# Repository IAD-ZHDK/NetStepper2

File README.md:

# NetStepper2
A networked stepper motor controller based on the ESP-WROOM-32 and the L6470. Examples built with netStepper can be seen in this [video](https://vimeo.com/278343342).  

## Parts

### Controllers

- Stepper Controller: `L6470` ([Datasheet](https://www.mouser.com/ds/2/389/l6470-954753.pdf), [Mouser](https://www.mouser.ch/ProductDetail/STMicroelectronics/L6470H?qs=sGAEpiMZZMuP%2fQeRSdvksPGSQkvtk%2fGb))
- SoC: `ESP-WROOM-32` ([Datasheet](https://espressif.com/sites/default/files/documentation/esp-wroom-32_datasheet_en.pdf), [Mouser](https://www.mouser.ch/ProductDetail/Adafruit/3320?qs=%2fha2pyFaduhvAZY8Ie1SD0odCwfSxZwX5aiqddL%252ba6k%3d))
- USB/UART: `CP2104` ([Datasheet](https://www.mouser.com/ds/2/368/cp2104-37496.pdf), [Mouser](https://www.mouser.ch/ProductDetail/Silicon-Labs/CP2104-F03-GMR?qs=sGAEpiMZZMtXqW1IUNX6MBk8lKhQ2c4Y))

### Interface

- RGB LED: `CLMVB-FKA-CFHEHLCBB7a363` ([Datasheet](https://www.mouser.com/ds/2/90/CLMVBFKA-276021.pdf), [Mouser](https://www.mouser.ch/ProductDetail/Cree-Inc/CLMVB-FKA-CFHEHLCBB7a363/?qs=sGAEpiMZZMvyj6n1w4pZD44mowbLOn3YXn9F0G7z9j4=))
- Micro USB: `ZX62-B-5PA(33)` ([Datasheet](https://www.mouser.com/ds/2/185/ZX_catalog-939768.pdf), [Mouser](https://www.mouser.ch/ProductDetail/Hirose-Connector/ZX62-B-5PA33?qs=%2fha2pyFadujrkQEnlOn9YJamDi2lLfztUsBlF%252bMpnrr%2ffu%252bTTtxTbg%3d%3d))

### Other

- NPN Transistor: `MMBT2222` ([Datasheet](https://www.mouser.com/ds/2/308/MMBT2222LT1-D-80103.pdf), [Mouser](https://www.mouser.ch/ProductDetail/863-SMMBT2222ALT3G?r=863-SMMBT2222ALT3G))
- Double Diodes: `BAV99` ([Datasheet](https://www.mouser.com/ds/2/308/BAV99-1118535.pdf), [Mouser](https://www.mouser.ch/ProductDetail/ON-Semiconductor-Fairchild/BAV99?qs=sGAEpiMZZMudZehw8RjeZe6BnmRwGdH1))
- Traco: `TSR 1-2433`: ([Datasheet](https://www.mouser.com/ds/2/687/tsr1-537631.pdf), [Mouser](https://www.mouser.ch/ProductDetail/TRACO-Power/TSR-1-2433?qs=sGAEpiMZZMsF1ODjcwEocIuESINJH25XntreftV5zWI%3d))
- Button: `B3AL1002P-MS`: ([Datasheet](https://www.mouser.com/ds/2/307/en-b3al-6968.pdf), [Mouser](https://www.mouser.ch/ProductDetail/Omron-Electronics/B3AL-1002P?qs=sGAEpiMZZMsgGjVA3toVBH4vymNSXBJAvFITsJt6vAk%3d))
- Power Jack: `PTH-Lock`: ([Datasheet](https://www.sparkfun.com/datasheets/Prototyping/Barrel-Connector-PJ-202A.pdf), [Mouser](https://www.mouser.ch/ProductDetail/SparkFun/PRT-00119?qs=%2fha2pyFaduhW%2fk%2fYYulWfhGNKo7ZHzyg2PgAdV2a06daJ1r7ZioXdg%3d%3d))
- Tantalum Capacitor: `10uF`: ([Datasheet](https://www.mouser.com/ds/2/40/f93-776559.pdf), [Mouser](https://www.mouser.ch/ProductDetail/AVX/F931D106MAA?qs=%2fha2pyFadugBNWncAbXQXxEHQJISJiFBJ7QXp8FDj7ScO5vdUpgUZA%3d%3d))
- Tantalum Capacitor: `47uF`: ([Datasheet](https://www.mouser.com/ds/2/40/f93-776559.pdf), [Mouser](https://www.mouser.ch/ProductDetail/AVX/F931A476KBA?qs=sGAEpiMZZMuEN2agSAc2puC4lhRhLeolV5NgMLhJRWs%3d))
- Electrolyte Capacitor: `100uF`: ([Datasheet](https://www.mouser.com/ds/2/88/SML%20series-552997.pdf), [Mouser](https://www.mouser.ch/ProductDetail/Illinois-Capacitor-CDE/107SML063M?qs=%2fha2pyFaduhe2UJZSX2WvbxZYvhC4L3TD5ZVG2tL5rqP%252bovMAc8Hgw%3d%3d))

## Notes

- ESP32 from Adafruit do not come in a tape/reel.

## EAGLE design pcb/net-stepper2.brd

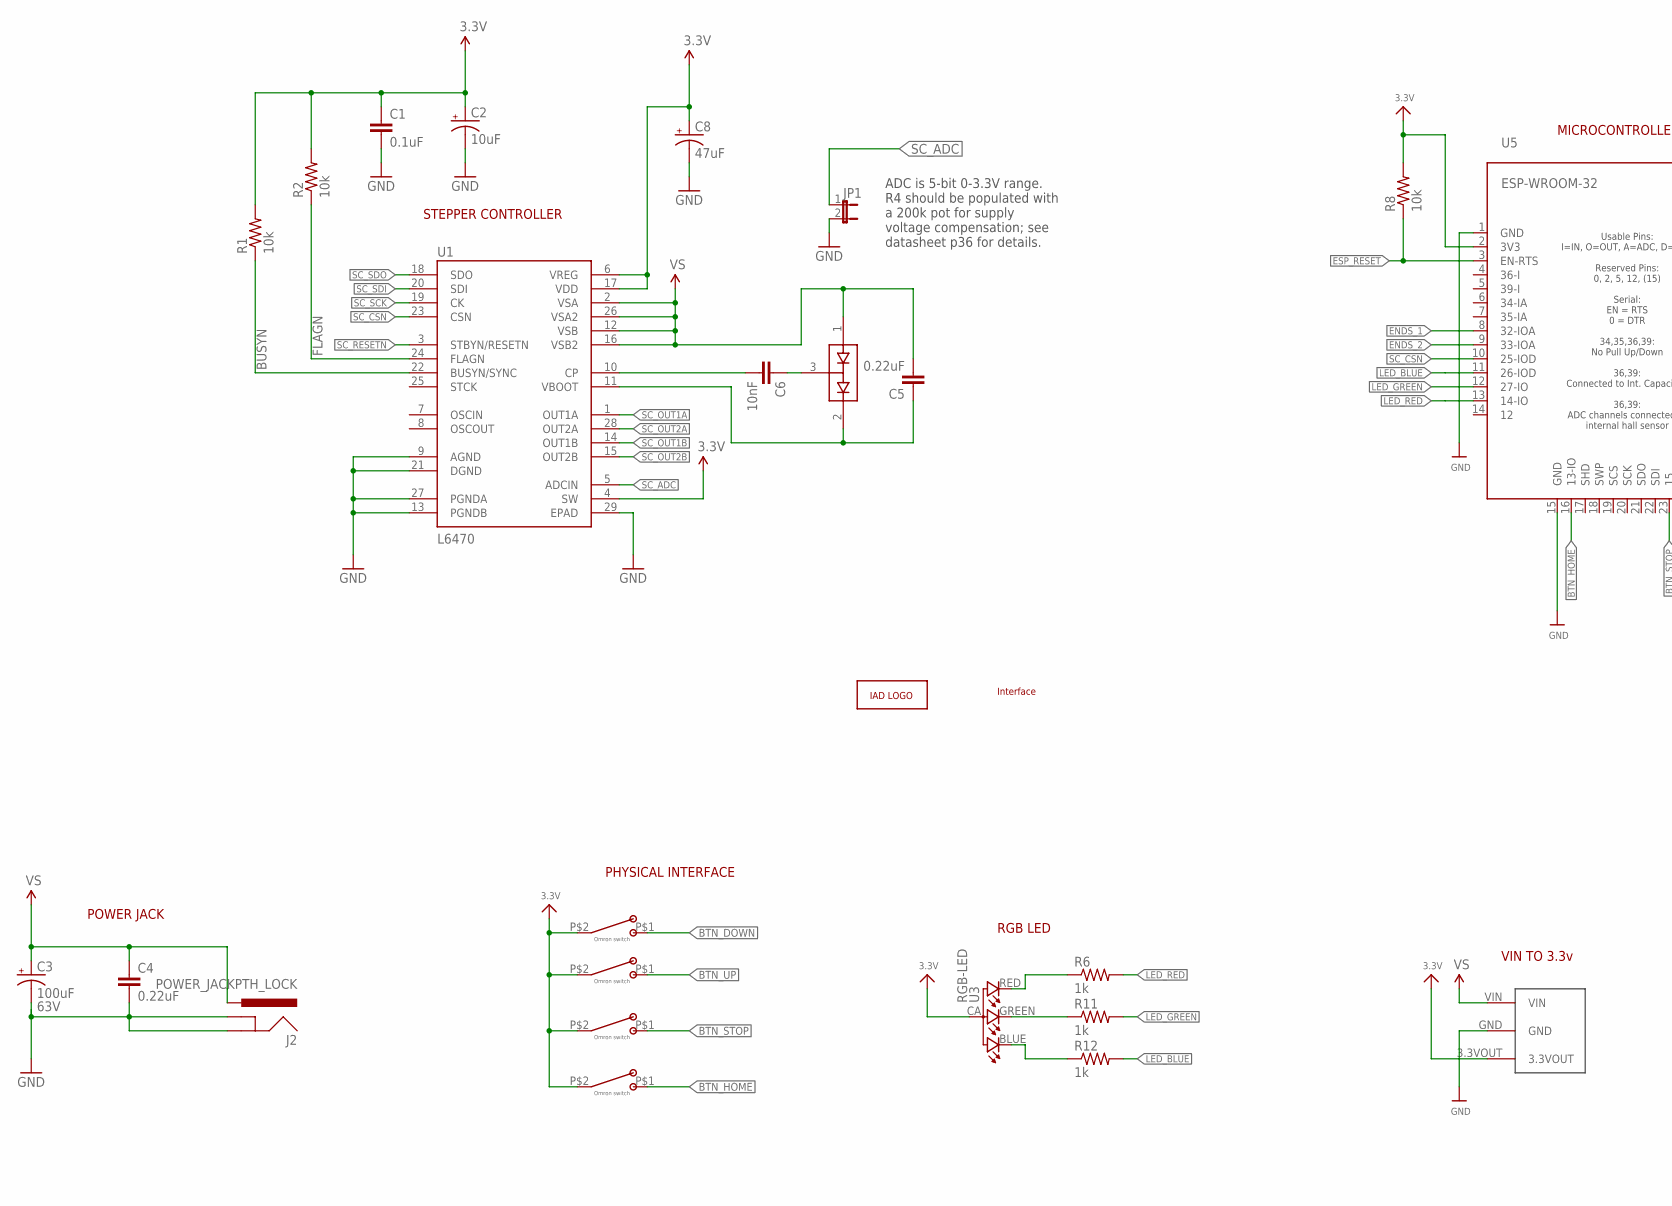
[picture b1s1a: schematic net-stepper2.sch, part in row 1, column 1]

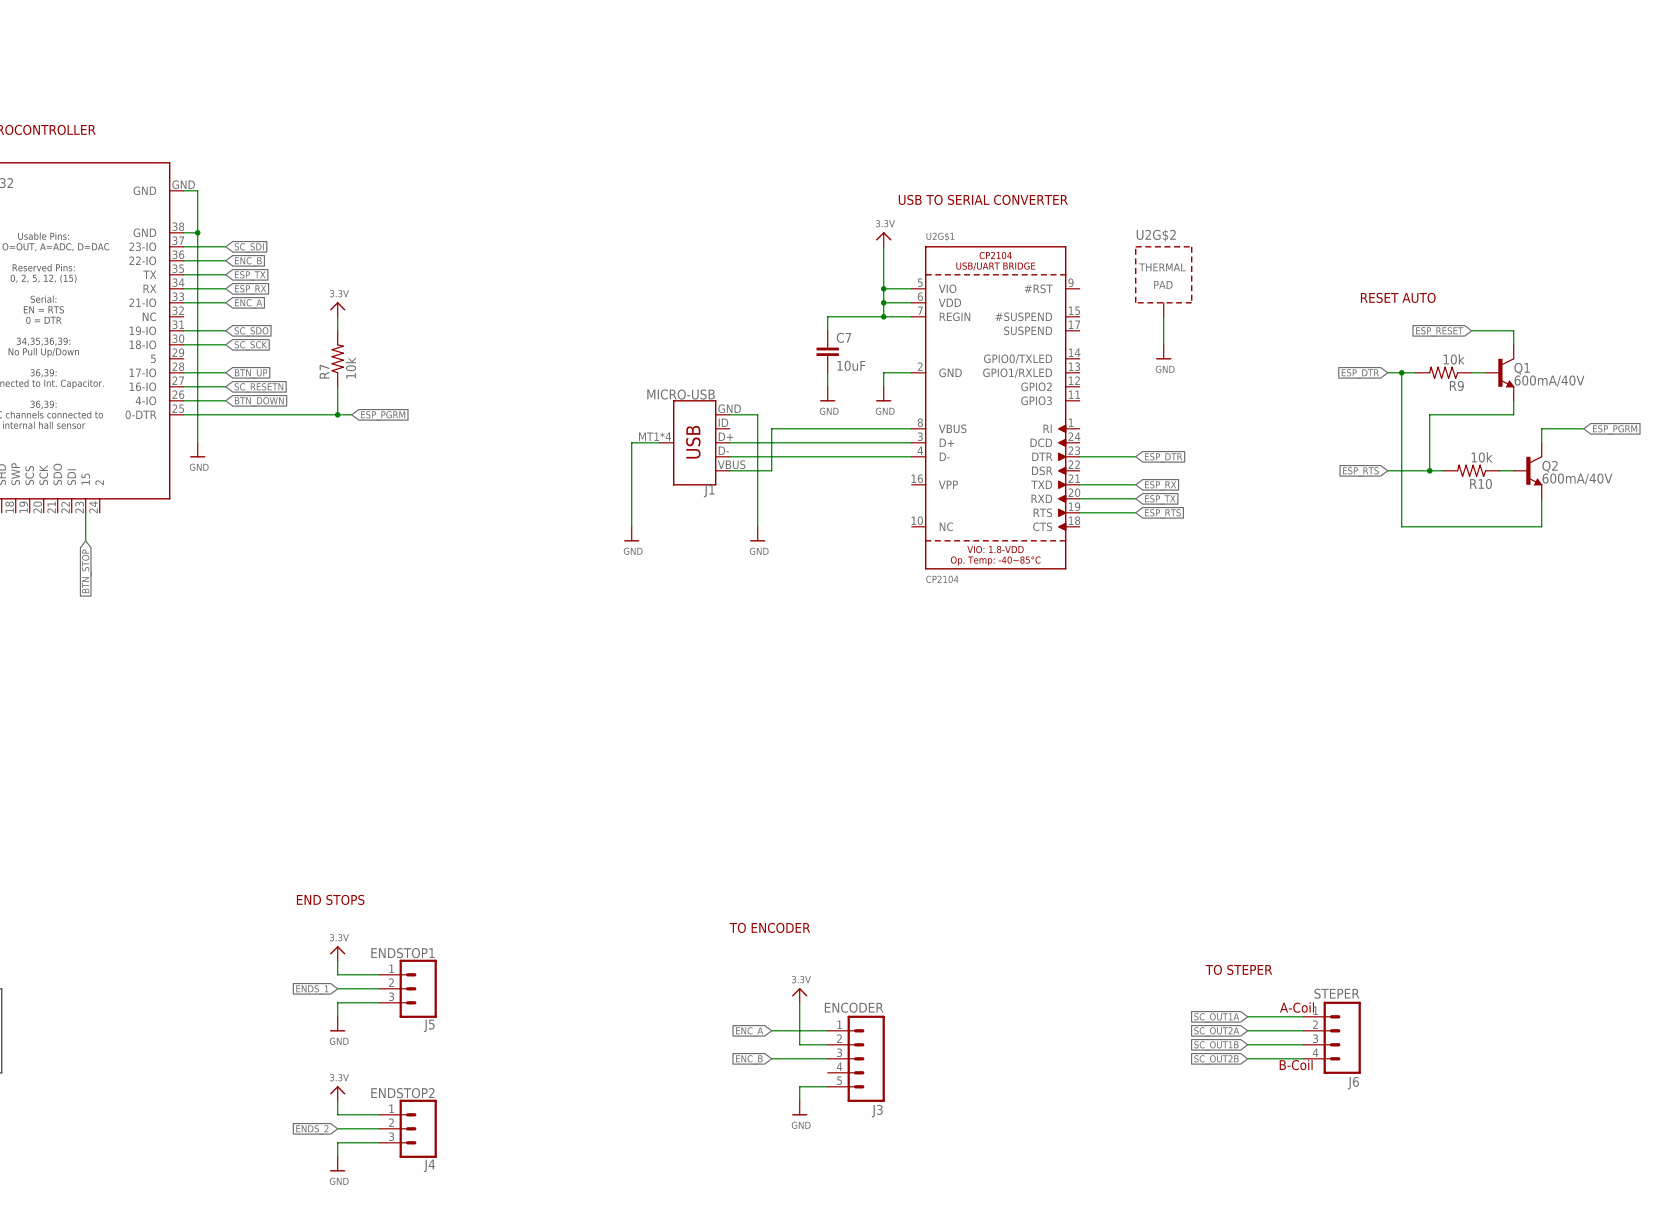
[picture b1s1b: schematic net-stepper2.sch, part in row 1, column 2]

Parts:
A1: ZHDK_LOGO_METAL; ZHDK_LOGO
A2: INTERFACE_NETSTEPPER
C1: 0.1uF; 0603-CAP
C2: 10uF; EIA3216
C3: 100uF; NIC_10X10.5_CAP
C4, C5: 0.22uF; 0603-CAP
C6: 10nF; 0603-CAP
C7: 10uF; 0603
C8: 47uF; EIA3528
D1: BAV99; SOT23-3@1
J1: MICRO-USB; USB-MICROB
J2: POWER_JACKPTH_LOCK; POWER_JACK_PTH_LOCK
J3: ENCODER; 1X05
J4: ENDSTOP2; 1X03
J5: ENDSTOP1; 1X03
J6: STEPER; 1X04_LOCK_LONGPADS
JP1: JUMPER-2SMD-NC; SJ_2S
Q1, Q2: 600mA/40V; SOT23-3
R1, R2, R7, R8, R9, R10: 10k; 0603-RES
R6, R11, R12: 1k; 0603-RES
S1, S2, S3, S4: B3AL-1002P-MS
U1: L6470; HTSSOP28
U2: CP2104; QFN24_4MM_SMSC
U3: RGB-LED; PLCC4-2MM-RGB
U4: TRACO12433
U5: ESP-WROOM-32

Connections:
3.3V: C1.1, C2.A (+), C7.1, C8.A (+), J3.2, J4.1, J5.1, R1.2, R2.2, R7.2, R8.2, S1.P$2, S2.P$2, S3.P$2, S4.P$2, U1.4 (SW), U1.6 (VREG), U1.17 (VDD), U2.5 (VIO), U2.6 (VDD), U2.7 (REGIN), U3.CA (1), U4.3.3VOUT, U5.2 (3V3)
BTN_DOWN: S1.P$1, U5.26 (4-IO)
BTN_HOME: S4.P$1, U5.16 (13-IO)
BTN_STOP: S3.P$1, U5.23 (15)
BTN_UP: S2.P$1, U5.28 (17-IO)
BUSYN: R1.1, U1.22 (BUSYN/SYNC)
CP_HIGH: C6.1, D1.3 (COM)
ENC_A: J3.1, U5.33 (21-IO)
ENC_B: J3.3, U5.36 (22-IO)
ENDS_1: J5.2, U5.8 (32-IOA)
ENDS_2: J4.2, U5.9 (33-IOA)
ESP_DTR: Q2.2 (E), R9.2, U2.23 (DTR)
ESP_PGRM: Q2.3 (C), R7.1, U5.25 (0-DTR)
ESP_RESET: Q1.3 (C), R8.1, U5.3 (EN-RTS)
ESP_RTS: Q1.2 (E), R10.2, U2.19 (RTS)
ESP_RX: U2.21 (TXD), U5.34 (RX)
ESP_TX: U2.20 (RXD), U5.35 (TX)
FLAGN: R2.1, U1.24 (FLAGN)
GND: C1.2, C2.C (-), C3.-, C4.2, C7.2, C8.C (-), J1.GND, J1.MT1 (SHIELD), J1.MT2 (SHIELD), J1.P$1 (SHIELD), J1.P$2 (SHIELD), J2.GND, J2.GNDBREAK, J3.5, J4.3, J5.3, JP1.2, U1.9 (AGND), U1.13 (PGNDB), U1.21 (DGND), U1.27 (PGNDA), U1.29 (EPAD), U2.2 (GND), U2.THERM (TP), U4.GND, U5.1 (GND), U5.15 (GND), U5.38 (GND), U5.GND
LED_BLUE: R12.2, U5.11 (26-IOD)
LED_GREEN: R11.2, U5.12 (27-IO)
LED_RED: R6.2, U5.13 (14-IO)
unnamed: J1.VBUS, U2.8 (VBUS)
unnamed: R11.1, U3.GREEN (3)
unnamed: R6.1, U3.RED (4)
unnamed: J1.D+, U2.3 (D+)
unnamed: J1.D-, U2.4 (D-)
unnamed: R12.1, U3.BLUE (2)
unnamed: Q1.1 (B), R9.1
unnamed: Q2.1 (B), R10.1
SC_ADC: JP1.1, U1.5 (ADCIN)
SC_CSN: U1.23 (CSN), U5.10 (25-IOD)
SC_OUT1A: J6.1, U1.1 (OUT1A)
SC_OUT1B: J6.3, U1.14 (OUT1B)
SC_OUT2A: J6.2, U1.28 (OUT2A)
SC_OUT2B: J6.4, U1.15 (OUT2B)
SC_RESETN: U1.3 (STBYN/RESETN), U5.27 (16-IO)
SC_SCK: U1.19 (CK), U5.30 (18-IO)
SC_SDI: U1.20 (SDI), U5.37 (23-IO)
SC_SDO: U1.18 (SDO), U5.31 (19-IO)
VS: C3.+, C4.1, C5.2, D1.1 (A1), J2.PWR, U1.2 (VSA), U1.12 (VSB), U1.16 (VSB2), U1.26 (VSA2), U4.VIN
V_BOOT: C5.1, D1.2 (C2), U1.11 (VBOOT)
V_CP: C6.2, U1.10 (CP)

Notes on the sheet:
63V
B-Coil
A-Coil
ADC is 5-bit 0-3.3V range. R4 should be populated with a 200k pot for supply voltage compensation; see datasheet p36 for details.
MICROCONTROLLER
RESET AUTO
END STOPS
VIN TO 3.3v
TO ENCODER
PHYSICAL INTERFACE
TO STEPER
POWER JACK
STEPPER CONTROLLER
USB TO SERIAL CONVERTER
RGB LED

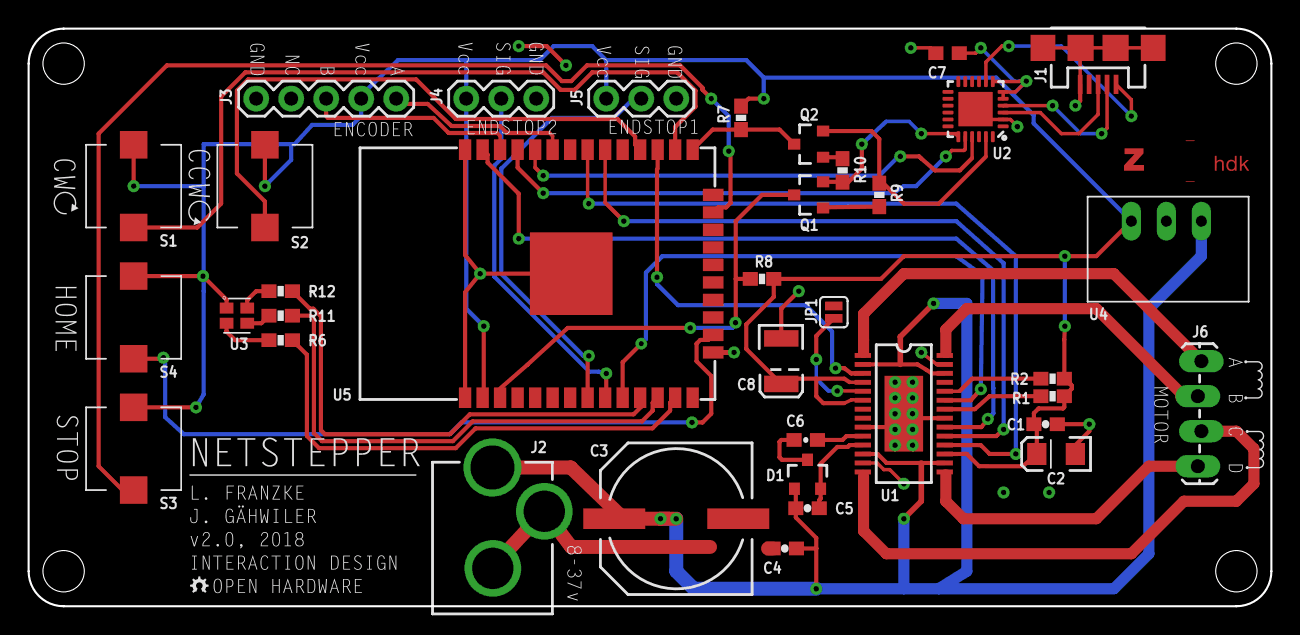
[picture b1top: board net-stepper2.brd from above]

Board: 2 copper layers, 90.2 x 41.9 mm, 38 parts (0 on the bottom side), 43 nets.

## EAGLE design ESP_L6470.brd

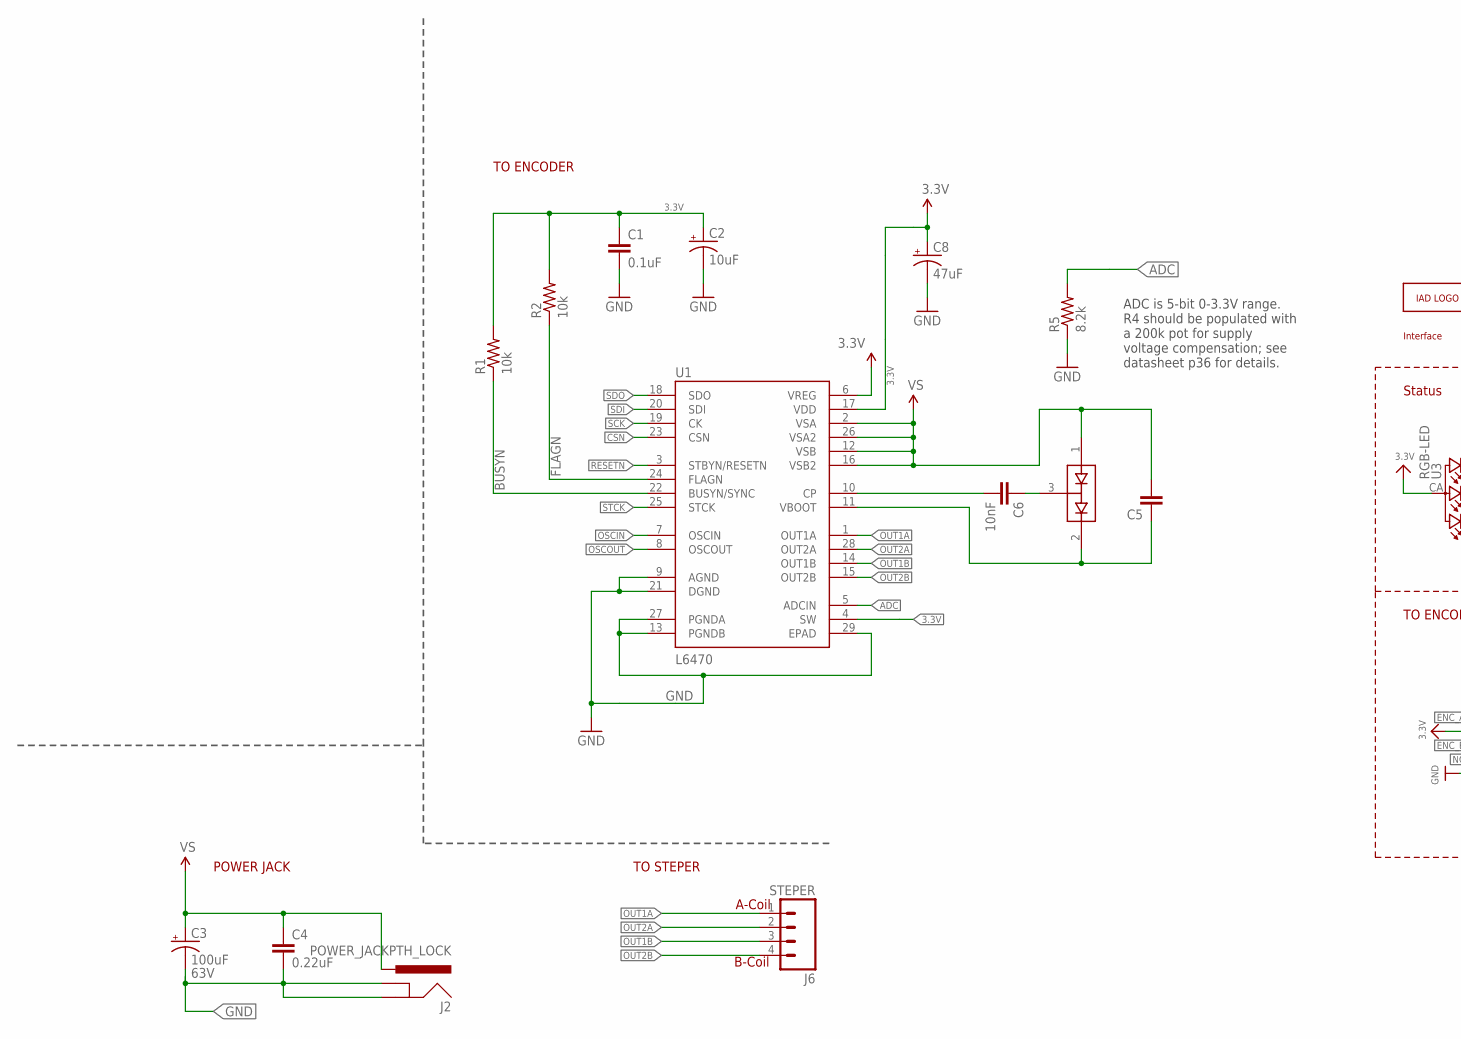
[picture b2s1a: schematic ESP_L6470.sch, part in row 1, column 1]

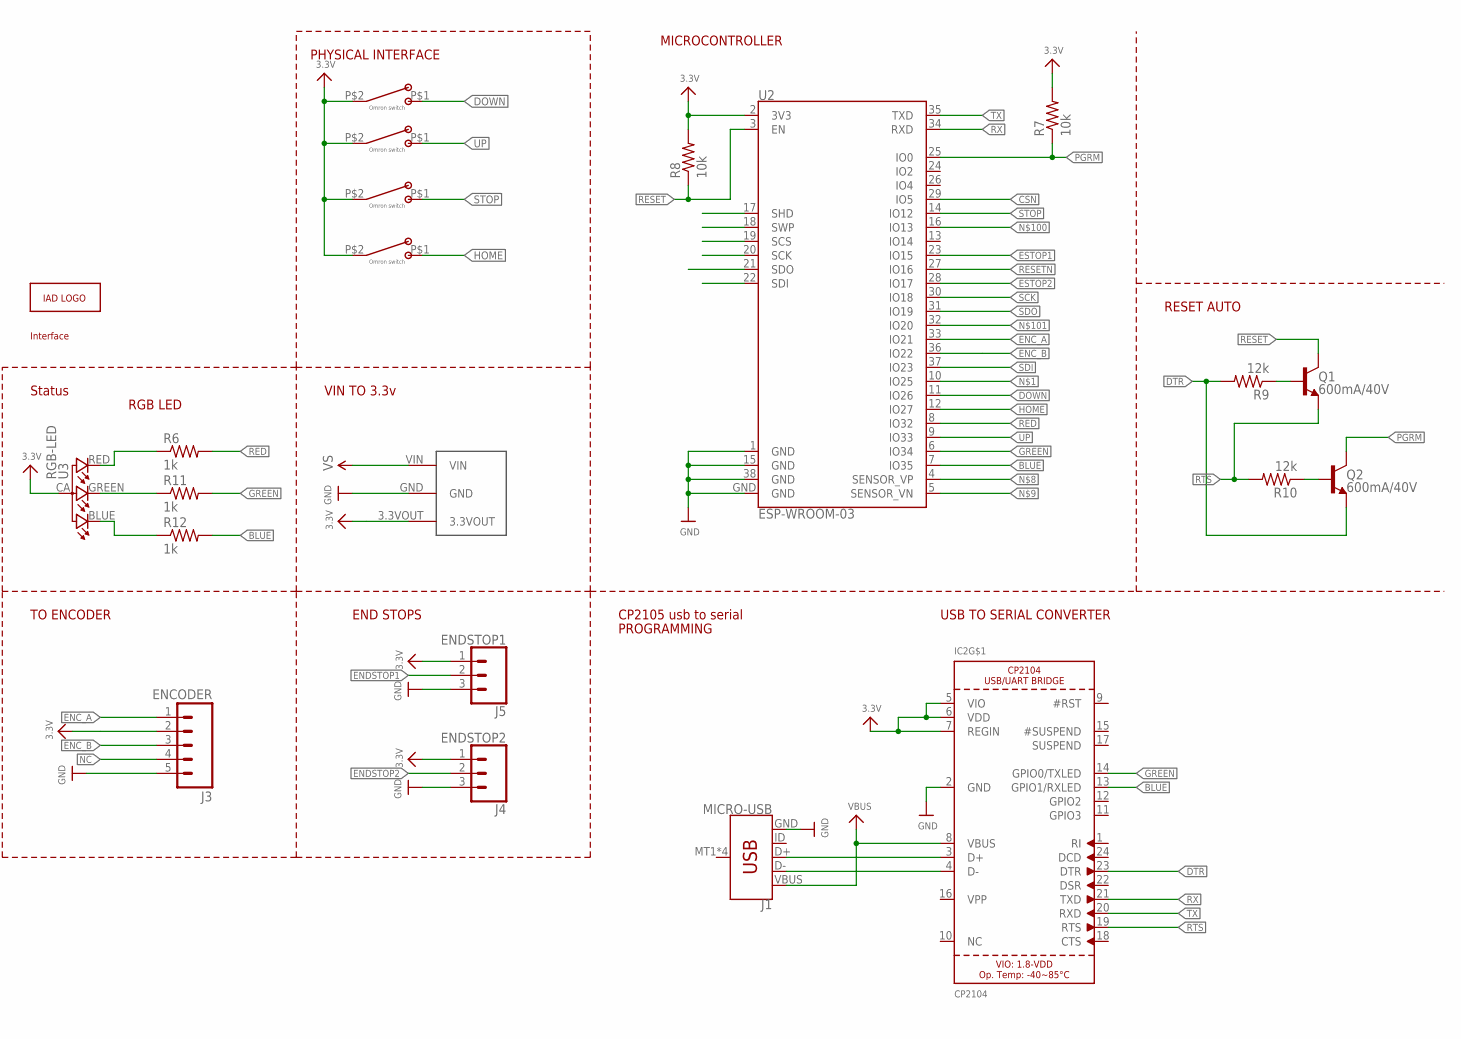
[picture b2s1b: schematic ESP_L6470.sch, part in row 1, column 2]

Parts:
A1: ZHDK_LOGO_METAL; ZHDK_LOGO
A2: INTERFACE_NETSTEPPER
C1: 0.1uF; 0603-CAP
C2: 10uF; EIA3216
C3: 100uF; NIC_10X10.5_CAP
C4, C5: 0.22uF; 0603-CAP
C6: 10nF; 0603-CAP
C8: 47uF; EIA3528
D1: BAV99; SOT23-3@1
IC2: CP2104; QFN24_4MM_SMSC
J1: MICRO-USB; USB-MICROB
J2: POWER_JACKPTH_LOCK; POWER_JACK_PTH_LOCK
J3: ENCODER; 1X05
J4: ENDSTOP2; 1X03
J5: ENDSTOP1; 1X03
J6: STEPER; 1X04_LOCK_LONGPADS
Q1, Q2: 600mA/40V; SOT23-3
R1, R2, R7, R8: 10k; 0603-RES
R5: 8.2k; 0603-RES
R6, R11, R12: 1k; 0603-RES
R9, R10: 12k; 0603-RES
S1, S2, S3, S4: B3AL-1002P-MS
U1: L6470; HTSSOP28
U2: ESP-WROOM-03
U3: RGB-LED; PLCC4-2MM-RGB
U4: TRACO12433

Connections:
3.3V: C1.1, C2.A (+), C8.A (+), IC2.5 (VIO), IC2.6 (VDD), IC2.7 (REGIN), J3.2, J4.1, J5.1, R1.2, R2.2, R7.2, R8.2, S1.P$2, S2.P$2, S3.P$2, S4.P$2, U1.4 (SW), U1.6 (VREG), U1.17 (VDD), U2.2 (3V3), U3.CA (1), U4.3.3VOUT
ADC: R5.2, U1.5 (ADCIN)
BLUE: IC2.13 (GPIO1/RXLED), R12.2, U2.7 (IO35)
BUSYN: R1.1, U1.22 (BUSYN/SYNC)
CP_HIGH: C6.1, D1.3 (COM)
CSN: U1.23 (CSN), U2.29 (IO5)
DOWN: S1.P$1, U2.11 (IO26)
DTR: IC2.23 (DTR), Q2.2 (E), R9.2
ENC_A: J3.1, U2.33 (IO21)
ENC_B: J3.3, U2.36 (IO22)
ENDSTOP1: J5.2
ENDSTOP2: J4.2
ESTOP1: U2.23 (IO15)
ESTOP2: U2.28 (IO17)
FLAGN: R2.1, U1.24 (FLAGN)
GND: C1.2, C2.C (-), C3.-, C4.2, C8.C (-), IC2.2 (GND), J1.GND, J2.GND, J2.GNDBREAK, J3.5, J4.3, J5.3, R5.1, U1.9 (AGND), U1.13 (PGNDB), U1.21 (DGND), U1.27 (PGNDA), U1.29 (EPAD), U2.1 (GND), U2.15 (GND), U2.38 (GND), U2.GND, U4.GND
GREEN: IC2.14 (GPIO0/TXLED), R11.2, U2.6 (IO34)
HOME: S4.P$1, U2.12 (IO27)
unnamed: R11.1, U3.GREEN (3)
unnamed: R6.1, U3.RED (4)
unnamed: IC2.3 (D+), J1.D+
unnamed: IC2.4 (D-), J1.D-
unnamed: R12.1, U3.BLUE (2)
unnamed: Q1.1 (B), R9.1
unnamed: Q2.1 (B), R10.1
NC: J3.4
OSCIN: U1.7 (OSCIN)
OSCOUT: U1.8 (OSCOUT)
OUT1A: J6.1, U1.1 (OUT1A)
OUT1B: J6.3, U1.14 (OUT1B)
OUT2A: J6.2, U1.28 (OUT2A)
OUT2B: J6.4, U1.15 (OUT2B)
PGRM: Q2.3 (C), R7.1, U2.25 (IO0)
RED: R6.2, U2.8 (IO32)
RESET: Q1.3 (C), R8.1, U2.3 (EN)
RESETN: U1.3 (STBYN/RESETN), U2.27 (IO16)
RTS: IC2.19 (RTS), Q1.2 (E), R10.2
RX: IC2.21 (TXD), U2.34 (RXD)
SCK: U1.19 (CK), U2.30 (IO18)
SDI: U1.20 (SDI), U2.37 (IO23)
SDO: U1.18 (SDO), U2.31 (IO19)
STCK: U1.25 (STCK)
STOP: S3.P$1, U2.14 (IO12)
TP: IC2.THERM (TP)
TX: IC2.20 (RXD), U2.35 (TXD)
UP: S2.P$1, U2.9 (IO33)
VBUS: IC2.8 (VBUS), J1.VBUS
VS: C3.+, C4.1, C5.2, D1.1 (A1), J2.PWR, U1.2 (VSA), U1.12 (VSB), U1.16 (VSB2), U1.26 (VSA2), U4.VIN
V_BOOT: C5.1, D1.2 (C2), U1.11 (VBOOT)
V_CP: C6.2, U1.10 (CP)

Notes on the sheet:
63V
B-Coil
A-Coil
ADC is 5-bit 0-3.3V range. R4 should be populated with a 200k pot for supply voltage compensation; see datasheet p36 for details.
MICROCONTROLLER
RESET AUTO
PROGRAMMING
END STOPS
VIN TO 3.3v
TO ENCODER
Status
PHYSICAL INTERFACE
CP2105 usb to serial
TO STEPER
POWER JACK
USB TO SERIAL CONVERTER
RGB LED

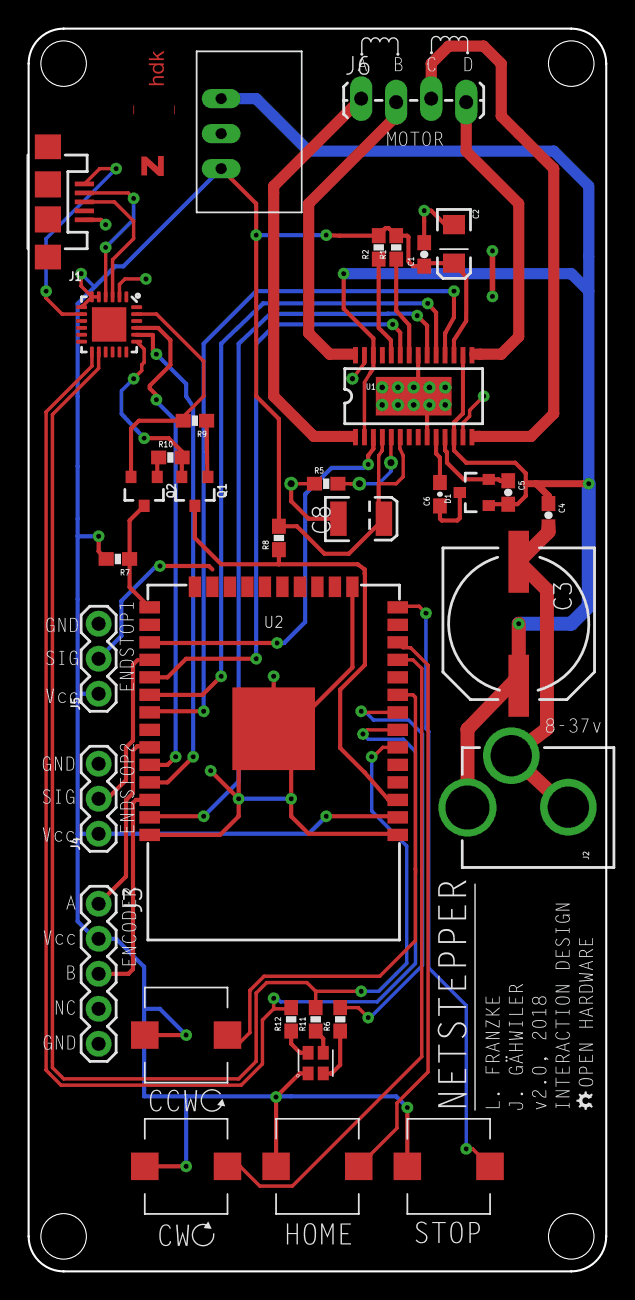
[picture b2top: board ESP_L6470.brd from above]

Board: 2 copper layers, 41.9 x 90.2 mm, 41 parts (0 on the bottom side), 41 nets.

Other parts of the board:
U$9, U$10, U$11, U$12: STAND-OFF

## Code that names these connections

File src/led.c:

#include <driver/ledc.h>

#include "led.h"

#define LED_RED_PIN 14
#define LED_GREEN_PIN 27
#define LED_BLUE_PIN 26

void led_init() {
  // prepare ledc timer config
  ledc_timer_config_t t = {
      .bit_num = LEDC_TIMER_10_BIT, .freq_hz = 5000, .speed_mode = LEDC_HIGH_SPEED_MODE, .timer_num = LEDC_TIMER_0};

  // configure ledc timer
  ESP_ERROR_CHECK(ledc_timer_config(&t));

  // prepare ledc channel config
  ledc_channel_config_t c = {
      .duty = 1024, .intr_type = LEDC_INTR_DISABLE, .speed_mode = LEDC_HIGH_SPEED_MODE, .timer_sel = LEDC_TIMER_0};

  // configure red led
  c.gpio_num = LED_RED_PIN;
  c.channel = LEDC_CHANNEL_0;
  ESP_ERROR_CHECK(ledc_channel_config(&c));

  // configure green led
  c.gpio_num = LED_GREEN_PIN;
  c.channel = LEDC_CHANNEL_1;
  ESP_ERROR_CHECK(ledc_channel_config(&c));

  // configure blue led
  c.gpio_num = LED_BLUE_PIN;
  c.channel = LEDC_CHANNEL_2;
  ESP_ERROR_CHECK(ledc_channel_config(&c));
}

void led_set(uint16_t r, uint16_t g, uint16_t b) {
  // set duties
  ESP_ERROR_CHECK(ledc_set_duty(LEDC_HIGH_SPEED_MODE, LEDC_CHANNEL_0, 1024 - r));
  ESP_ERROR_CHECK(ledc_set_duty(LEDC_HIGH_SPEED_MODE, LEDC_CHANNEL_1, 1024 - g));
  ESP_ERROR_CHECK(ledc_set_duty(LEDC_HIGH_SPEED_MODE, LEDC_CHANNEL_2, 1024 - b));

  // update channels
  ESP_ERROR_CHECK(ledc_update_duty(LEDC_HIGH_SPEED_MODE, LEDC_CHANNEL_0));
  ESP_ERROR_CHECK(ledc_update_duty(LEDC_HIGH_SPEED_MODE, LEDC_CHANNEL_1));
  ESP_ERROR_CHECK(ledc_update_duty(LEDC_HIGH_SPEED_MODE, LEDC_CHANNEL_2));
}

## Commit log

2018-01-30 bootstrapped naos
2018-01-30 implemented device status
2018-01-30 added art32
2018-01-30 added param handling
2018-01-30 clarified
2018-01-30 added more commands
2018-01-30 added rolling stop
2018-01-30 added wait command
2018-01-30 already done
2018-01-31 added more param getters and setters
2018-01-31 added calculations and more commands
2018-01-31 added missing command
2018-02-02 Board Layout and Schematic
2018-02-27 Update schematic with USB to Serial
2018-02-27 added some components
2018-02-28 update with USB to Serial
2018-03-02 Updated board
2018-03-05 Updated with silkscreen
2018-03-06 select all layers
2018-03-06 removed unused wire
2018-03-06 renamed some parts
2018-03-06 approved some errors
2018-03-06 renamed aesthetics
2018-03-06 fixed tx and rx pins and removed jumpers
2018-03-06 moved pcb to sub directory
2018-03-06 moved board
2018-03-06 replaced esp32 component
2018-03-06 removed unused signals
2018-03-06 reorganized schematics
2018-03-06 connect usb mounting pins to ground
2018-03-06 changed pull resistors to 10k in order remove one resistor family
2018-03-06 replaced cp2104 in order to connect the thermal pad to ground
2018-03-06 updated schematics
2018-03-06 added capacitor
2018-03-06 removed not needed ground plan vertices
2018-03-06 remapped pins
2018-03-06 prepared new routing
2018-03-06 Missing routing fixed
2018-03-07 added top ground plate
2018-03-07 rotated layout
2018-03-07 smashed comoponents and placed names
2018-03-07 removed todo
2018-03-07 approved error
2018-03-07 set via sizes and updated design rules to comply
2018-03-07 added missing name label
2018-03-07 exported image
2018-03-07 added readme
2018-03-07 added schematic pdf
2018-03-07 added bom and updated readme
2018-03-07 removed vr
2018-03-07 Last check
2018-03-07 updated label
2018-03-07 removec r5 from bom
2018-03-07 updated bom
2018-03-07 Drill size change
2018-03-07 updated exports
2018-03-21 fix project name
2018-03-21 stop motor when going offline
2018-03-21 implemented async button handling
2018-03-21 removed unused callbacks
2018-03-21 simplified
2018-03-22 make static
2018-03-22 renamed task
2018-03-22 block while receiving
2018-03-22 added encoder
2018-03-22 do not wrap task creation
2018-03-22 renamed enc to encoder
2018-03-22 remove auxillary constants file
2018-03-22 changed case
2018-03-22 do not implement advanced features
2018-03-22 removed unused stuff
2018-03-22 renamed
2018-03-22 renamed lots of things
2018-03-22 renamed params
2018-03-22 moved constants
2018-03-22 fixed
2018-03-22 small fixes
2018-03-22 make speeds configurable
2018-04-05 Fixed minor trace mistake
2018-04-09 set new buttons
2018-04-09 added led control
2018-04-09 added todo
2018-04-09 updated encoder pins
2018-04-09 updated chip select pin
2018-04-09 disabled position logging
2018-04-09 properly calculate revolutions
2018-04-09 moved
2018-04-09 added blocked mode
2018-04-09 set led to yellow in blocked mode
2018-04-09 bump version
2018-04-11 added end stop
2018-04-11 added logging
2018-04-11 added analog end stop mode
2018-04-11 use analog mode
2018-04-11 properly calculate real voltage
2018-04-11 added sharp converter
2018-04-12 updated firmware
2018-04-13 fix bug
2018-04-18 updated to new naos param api
2018-04-21 updated naos
2019-04-18 incerease max acceleration & deceleration
2019-04-18 updated defaults
2019-04-18 small fix
2019-04-18 exposed more parameters
2019-04-18 added gear ratio parameter
2019-04-18 added resolution parameter
2019-05-09 fix 22 bits clamping
2019-05-09 added helper to configure int based step mode
2019-05-09 init naos earlier
2019-05-09 fix typo
2019-05-09 renamed function
2019-05-09 fix usage of min and max
2019-05-09 added micro stepping parameter
2019-05-10 properly constrain target position
2019-05-10 simplify
2019-05-10 added led feedback for home position reset
2019-05-10 start always in blocked mode
2019-05-10 added parameters to constrain target
2019-05-21 added cockpit template
2019-05-24 smaller widgets

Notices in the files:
parts and their libraries:
SparkFun-Capacitors: Licensing: CC v3.0 Share-Alike You are welcome to use this library for commercial purposes.
microbuilder: This work is placed in the public domain, and may be freely used for commercial and non-commercial work with the following conditions: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
